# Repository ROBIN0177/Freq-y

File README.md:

# Freq-y
## Your Frequency Scanning Companion

I made this project because there isn't a cheap frequency scanner you can rely on. If you've built RF projects before, you know the pain of tracking down a signal leak, figuring out where it's coming from, what frequency it's on, and which device is causing it.

I ran into this myself: my home WiFi was getting choked by an unknown source. Turned out to be my own custom radio bleeding into the band. This scanner also lets you test how much shielding a material actually provides—whether it's a wall, a case, or a Faraday cage. Pinpoint the exact device causing interference easily. (Unlike me. Took 3 days to figure out..)

---

## Pictures

(Mind the hole, it's for a rocker switch I couldn't get a STL of.)

---

## BOM

Full BOM with DigiKey part numbers: see `/BOM/`

---

## File Structure

```
Freq-y/
├── CAD/
│   ├── enclosure_top.stl
│   └── enclosure_bottom.stl
├── PCB/
│   ├── Freq-y_Schem
|   ├── Freq-y_PCB
│   └── Freq-y_Pro
├── GERBER/
│   ├── Freq-y-B_Cu.gbr
│   ├── Freq-y-F_Cu.gbr
│   ├── Freq-y-B_Mask.gbr
│   ├── Freq-y-F_Mask.gbr
│   ├── Freq-y-B_Silkscreen.gbr
│   ├── Freq-y-F_Silkscreen.gbr
│   ├── Freq-y-Edge_Cuts.gbr
│   ├── Freq-y-B_Paste.gbr
│   ├── Freq-y-F_Paste.gbr
│   ├── Freq-y-NPTH.drl
│   ├── Freq-y-PTH.drl
│   └── Freq-y.zip
├── BOM/
│   ├── BOM_DigiKey.csv
│   └── BOM_AUX.csv
├── README.md
├── Journal.md
└── LICENSE
```

---

## Special Thanks

**Hack Club** — I couldn't have made this without it.

## NOTE

RF impedance was calculated to the nearest allowed mm. Any more would have severed and or created problems for other components!!
Range is limited due to it not having exact RF impedance!!

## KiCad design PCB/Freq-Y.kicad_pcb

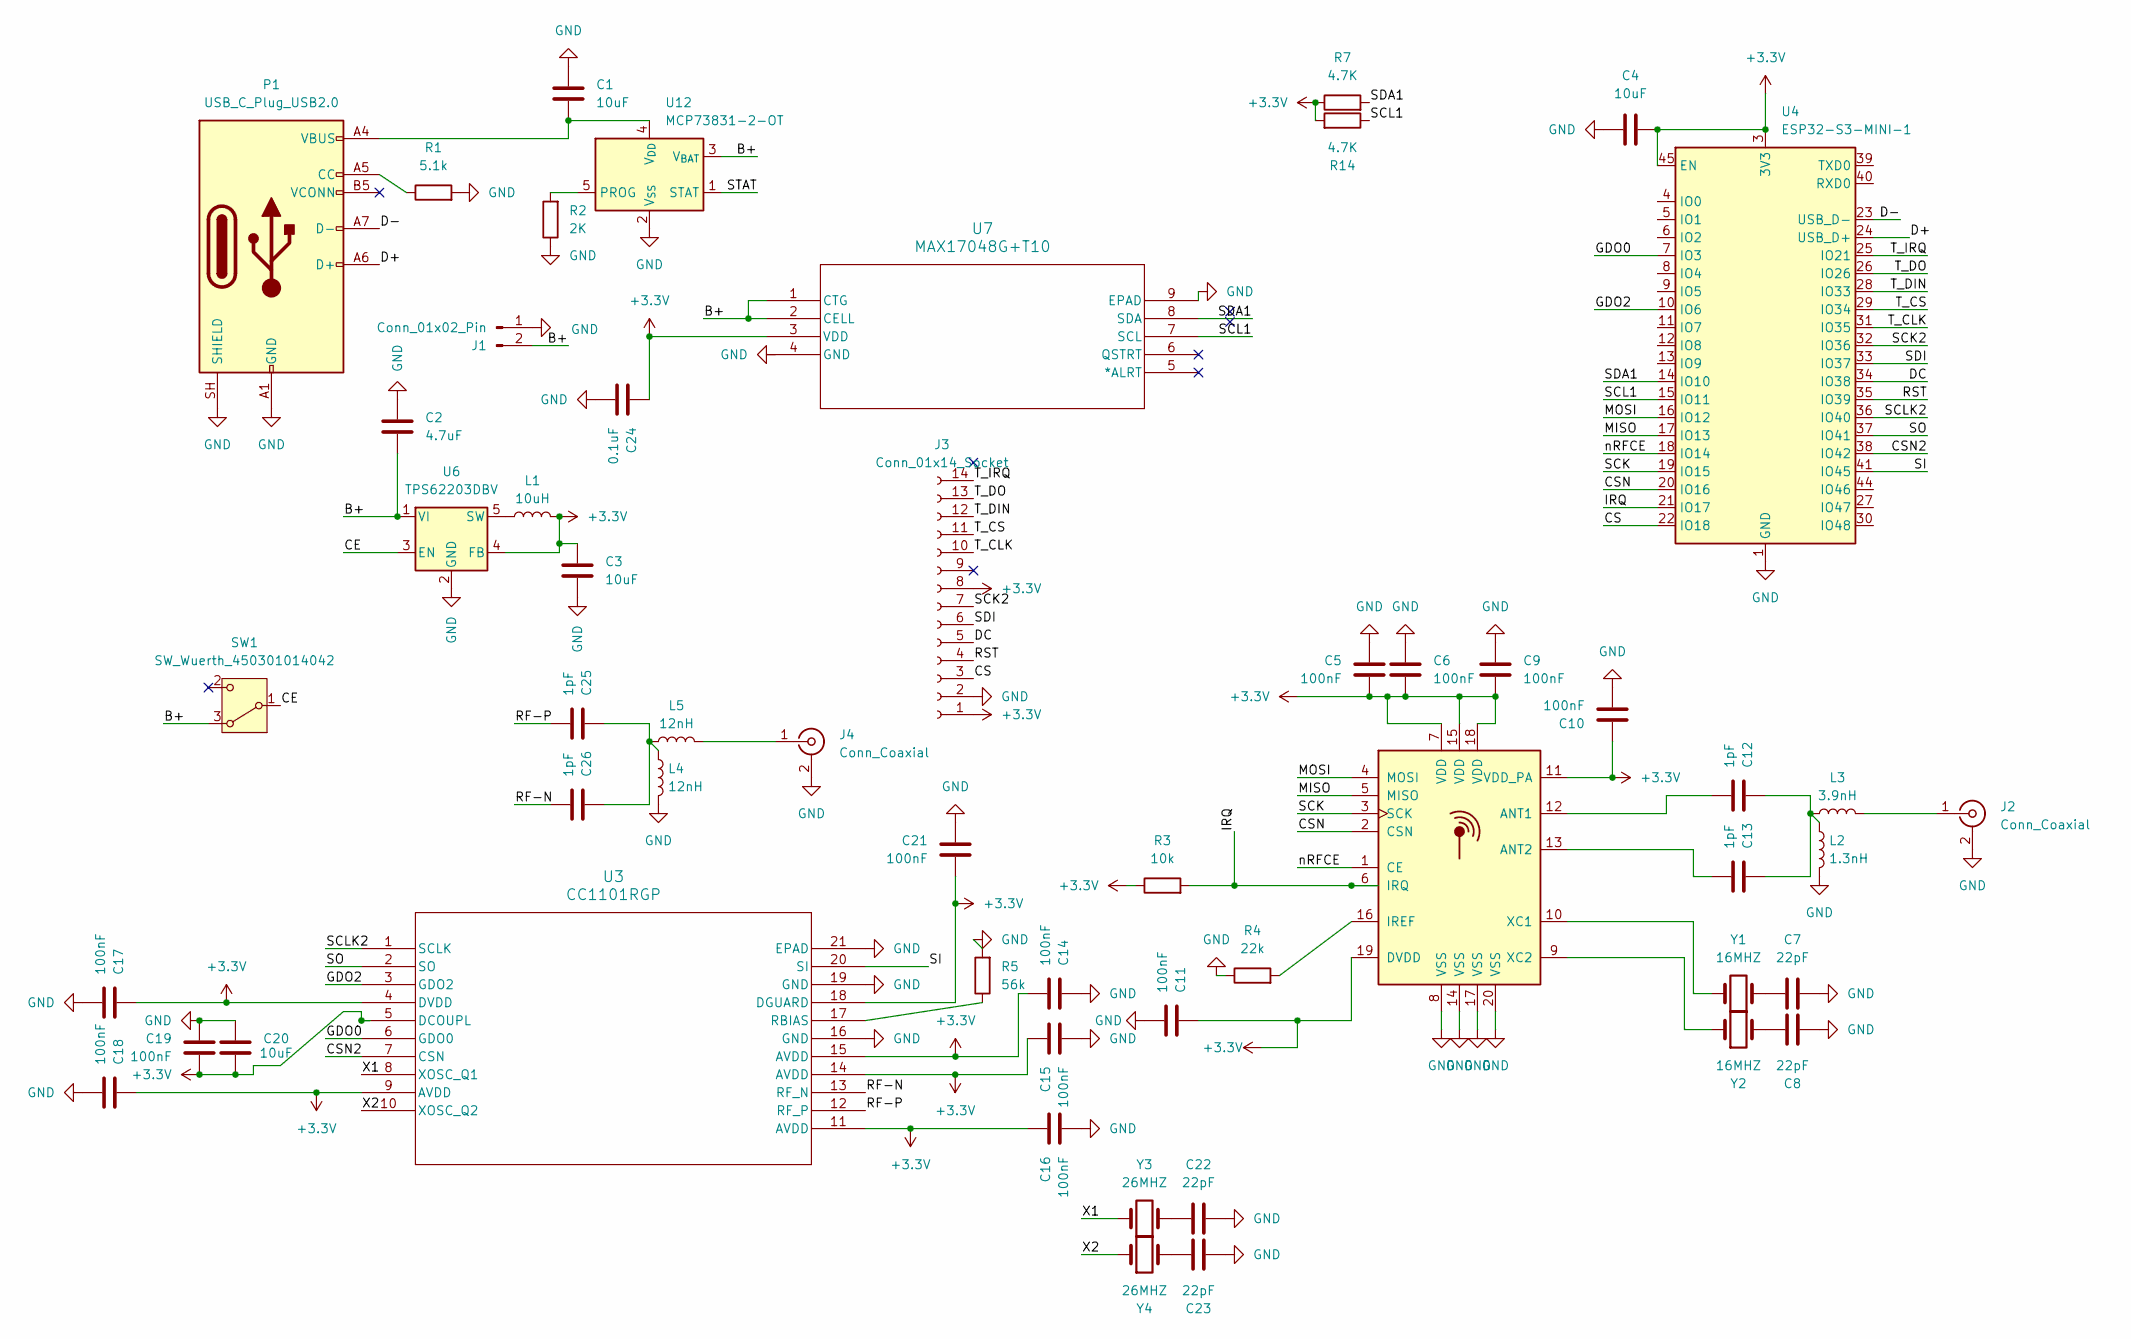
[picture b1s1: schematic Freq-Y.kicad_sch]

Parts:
C1, C3, C4, C20: 10uF; C_0603_1608Metric
C2: 4.7uF; C_0603_1608Metric
C5, C6, C9, C10, C11, C14, C15, C16, C17, C18, C19, C21: 100nF; C_0603_1608Metric
C7, C8, C22, C23: 22pF; C_0603_1608Metric
C12, C13, C25, C26: 1pF; C_0603_1608Metric
C24: 0.1uF; C_0603_1608Metric
J1: Conn_01x02_Pin; PinSocket_1x02_P1.00mm_Vertical
J2, J4: Conn_Coaxial; SMA_Molex_73251-1153_EdgeMount_Horizontal
J3: Conn_01x14_Socket; PinSocket_1x14_P2.54mm_Vertical
L1: 10uH; L_0805_2012Metric
L2: 1.3nH; L_0805_2012Metric
L3: 3.9nH; L_0805_2012Metric
L4, L5: 12nH; L_0805_2012Metric
P1: USB_C_Plug_USB2.0; USB_C_Receptacle_GCT_USB4105-xx-A_16P_TopMnt_Horizontal
R1: 5.1k; R_0603_1608Metric
R2: 2K; R_0603_1608Metric
R3: 10k; R_0603_1608Metric
R4: 22k; R_0603_1608Metric
R5: 56k; R_0603_1608Metric
R7, R14: 4.7K; R_0603_1608Metric
SW1: SW_Wuerth_450301014042; SW_Slide-03_Wuerth-WS-SLTV_10x2.5x6.4_P2.54mm
U2: nRF24L01P; QFN-20-1EP_4x4mm_P0.5mm_EP2.5x2.5mm
U3: CC1101RGP; RGP20_2P4X2P4
U4: ESP32-S3-MINI-1; ESP32-S2-MINI-1
U6: TPS62203DBV; SOT-23-5
U7: MAX17048G+T10; 21-0168E_T822-3_MXM
U12: MCP73831-2-OT; SOT-23-5
Y1, Y2: 16MHZ; Crystal_SMD_0603-2Pin_6.0x3.5mm
Y3, Y4: 26MHZ; Crystal_SMD_0603-2Pin_6.0x3.5mm

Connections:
+3.3V: C3.1, C4.2, C5.2, C6.2, C9.2, C10.1, C11.1, C14.2, C15.1, C16.1, C17.1, C18.1, C19.2, C20.2, C21.2, C24.1, J3.1, J3.8, L1.2, R3.1, R7.1, R14.2, U2.7 (VDD), U2.11 (VDD_PA), U2.15 (VDD), U2.18 (VDD), U2.19 (DVDD), U3.4 (DVDD), U3.5 (DCOUPL), U3.9 (AVDD), U3.11 (AVDD), U3.14 (AVDD), U3.15 (AVDD), U3.18 (DGUARD), U4.3 (3V3), U4.45 (EN), U6.4 (FB), U7.3 (VDD)
/B+: C2.1, J1.2, SW1.3 (A), U6.1 (VI), U7.1 (CTG), U7.2 (CELL), U12.3 (V_{BAT})
/CE: SW1.1 (B), U6.3 (EN)
/CS: J3.3, U4.22 (IO18)
/CSN: U2.2 (CSN), U4.20 (IO16)
/CSN2: U3.7 (CSN), U4.38 (IO42)
/D+: P1.A6 (D+), U4.24 (USB_D+)
/D-: P1.A7 (D-), U4.23 (USB_D-)
/DC: J3.5, U4.34 (IO38)
/GDO0: U3.6 (GDO0), U4.7 (IO3)
/GDO2: U3.3 (GDO2), U4.10 (IO6)
/IRQ: R3.2, U2.6 (IRQ), U4.21 (IO17)
/MISO: U2.5 (MISO), U4.17 (IO13)
/MOSI: U2.4 (MOSI), U4.16 (IO12)
/RF-N: C26.2, U3.13 (RF_N)
/RF-P: C25.2, U3.12 (RF_P)
/RST: J3.4, U4.35 (IO39)
/SCK: U2.3 (SCK), U4.19 (IO15)
/SCK2: J3.7, U4.32 (IO36)
/SCL1: R14.1, U4.15 (IO11), U7.7 (SCL)
/SCLK2: U3.1 (SCLK), U4.36 (IO40)
/SDA1: R7.2, U4.14 (IO10), U7.8 (SDA)
/SDI: J3.6, U4.33 (IO37)
/SI: U3.20 (SI), U4.41 (IO45)
/SO: U3.2 (SO), U4.37 (IO41)
/STAT: U12.1 (STAT)
/T_CLK: J3.10, U4.31 (IO35)
/T_CS: J3.11, U4.29 (IO34)
/T_DIN: J3.12, U4.28 (IO33)
/T_DO: J3.13, U4.26 (IO26)
/T_IRQ: J3.14, U4.25 (IO21)
/X1: U3.8 (XOSC_Q1), Y3.2
/X2: U3.10 (XOSC_Q2), Y4.1
/nRFCE: U2.1 (CE), U4.18 (IO14)
GND: C1.1, C2.2, C3.2, C4.1, C5.1, C6.1, C7.2, C8.1, C9.1, C10.2, C11.2, C14.1, C15.2, C16.2, C17.2, C18.2, C19.1, C20.1, C21.1, C22.2, C23.1, C24.2, J1.1, J2.2 (Ext), J3.2, J4.2 (Ext), L2.2, L4.2, P1.A1 (GND), P1.A12 (GND), P1.B1 (GND), P1.B12 (GND), P1.SH (SHIELD), R1.2, R2.1, R4.1, R5.2, U2.8 (VSS), U2.14 (VSS), U2.17 (VSS), U2.20 (VSS), U3.16 (GND), U3.19 (GND), U3.21 (EPAD), U4.1 (GND), U4.2 (GND), U4.42 (GND), U4.43 (GND), U4.46 (GND), U4.47 (GND), U4.48 (GND), U4.49 (GND), U4.50 (GND), U4.51 (GND), U4.52 (GND), U4.53 (GND), U4.54 (GND), U4.55 (GND), U4.56 (GND), U4.57 (GND), U4.58 (GND), U4.59 (GND), U4.60 (GND), U4.61 (GND), U4.62 (GND), U4.63 (GND), U4.64 (GND), U4.65 (GND), U6.2 (GND), U7.9 (EPAD), U12.2 (V_{SS})
unnamed: C7.1, Y1.1
unnamed: C8.2, Y2.2
unnamed: C12.1, C13.1, L2.1, L3.1
unnamed: C22.1, Y3.1
unnamed: C23.2, Y4.2
unnamed: C25.1, C26.1, L4.1, L5.1
unnamed: J2.1 (In), L3.2
unnamed: J4.1 (In), L5.2
unnamed: P1.A5 (CC), R1.1
unnamed: C12.2, U2.12 (ANT1)
unnamed: C13.2, U2.13 (ANT2)
unnamed: R4.2, U2.16 (IREF)
unnamed: U2.10 (XC1), Y1.2
unnamed: U2.9 (XC2), Y2.1
unnamed: R5.1, U3.17 (RBIAS)
unnamed: L1.1, U6.5 (SW)
unnamed: R2.2, U12.5 (PROG)
unnamed: C1.2, P1.A4 (VBUS), P1.A9 (VBUS), P1.B4 (VBUS), P1.B9 (VBUS), U12.4 (V_{DD})

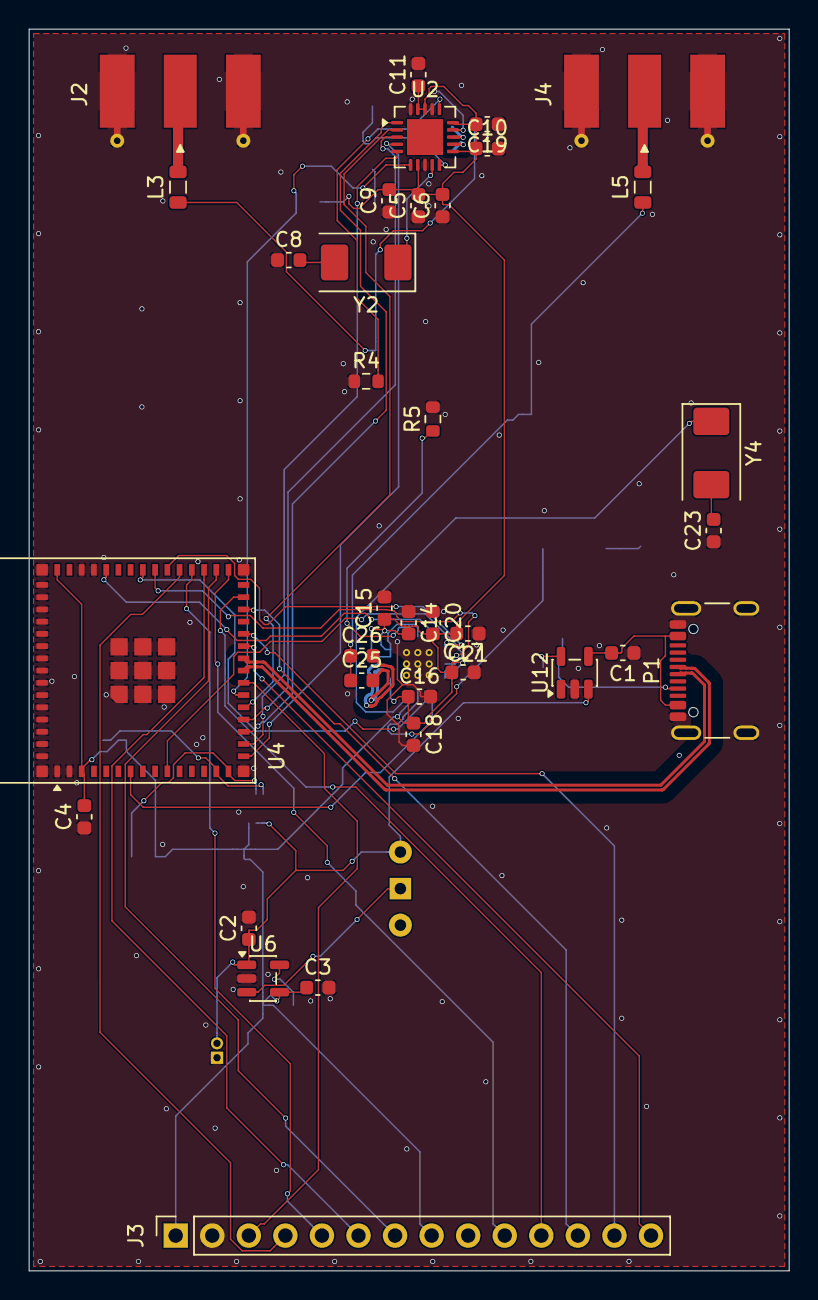
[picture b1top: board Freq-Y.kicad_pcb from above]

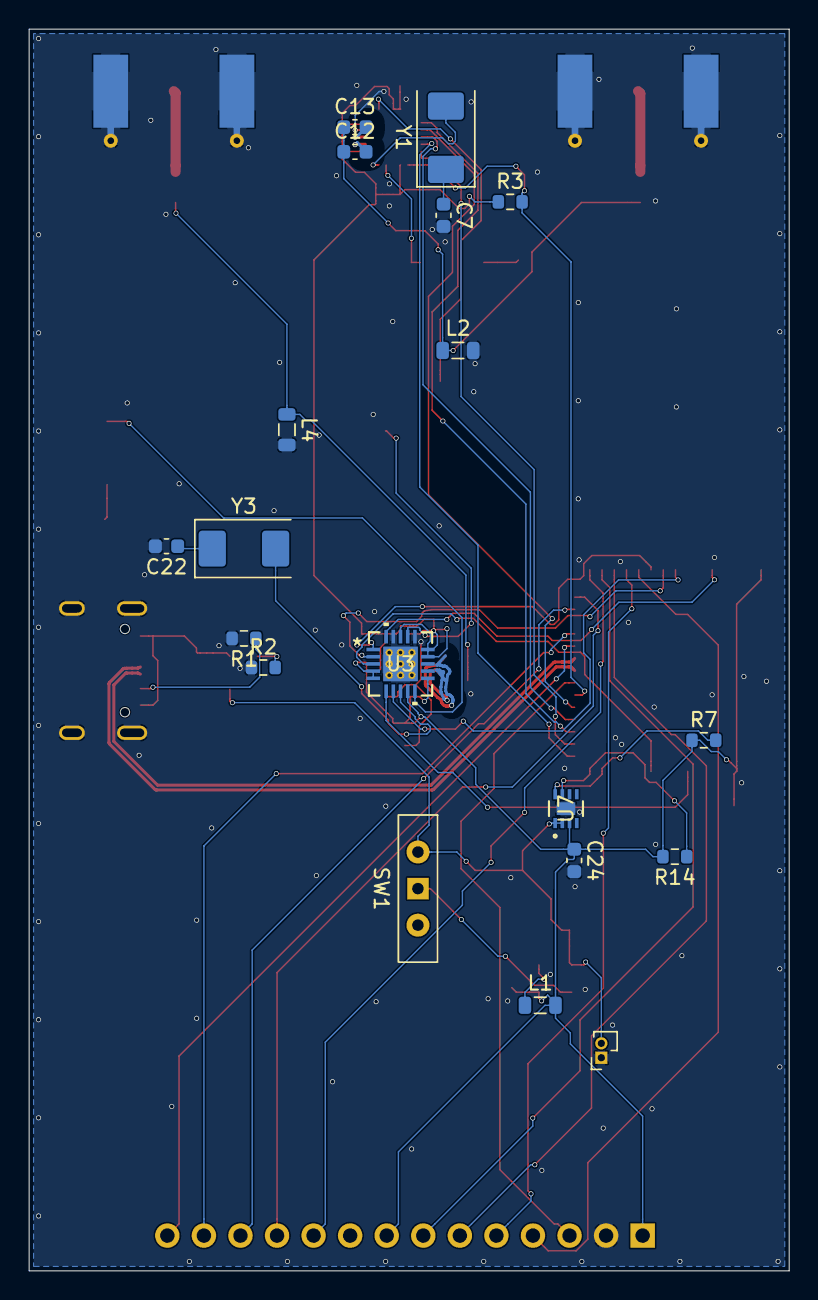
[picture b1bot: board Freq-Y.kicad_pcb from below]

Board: 2 copper layers, 52.8 x 86.3 mm, 54 parts (19 on the bottom side), 52 nets.
